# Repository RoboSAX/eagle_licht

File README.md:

# eagle_licht
Vereinfachte Platine für das Spielfeld des RoboSAX ab 2018

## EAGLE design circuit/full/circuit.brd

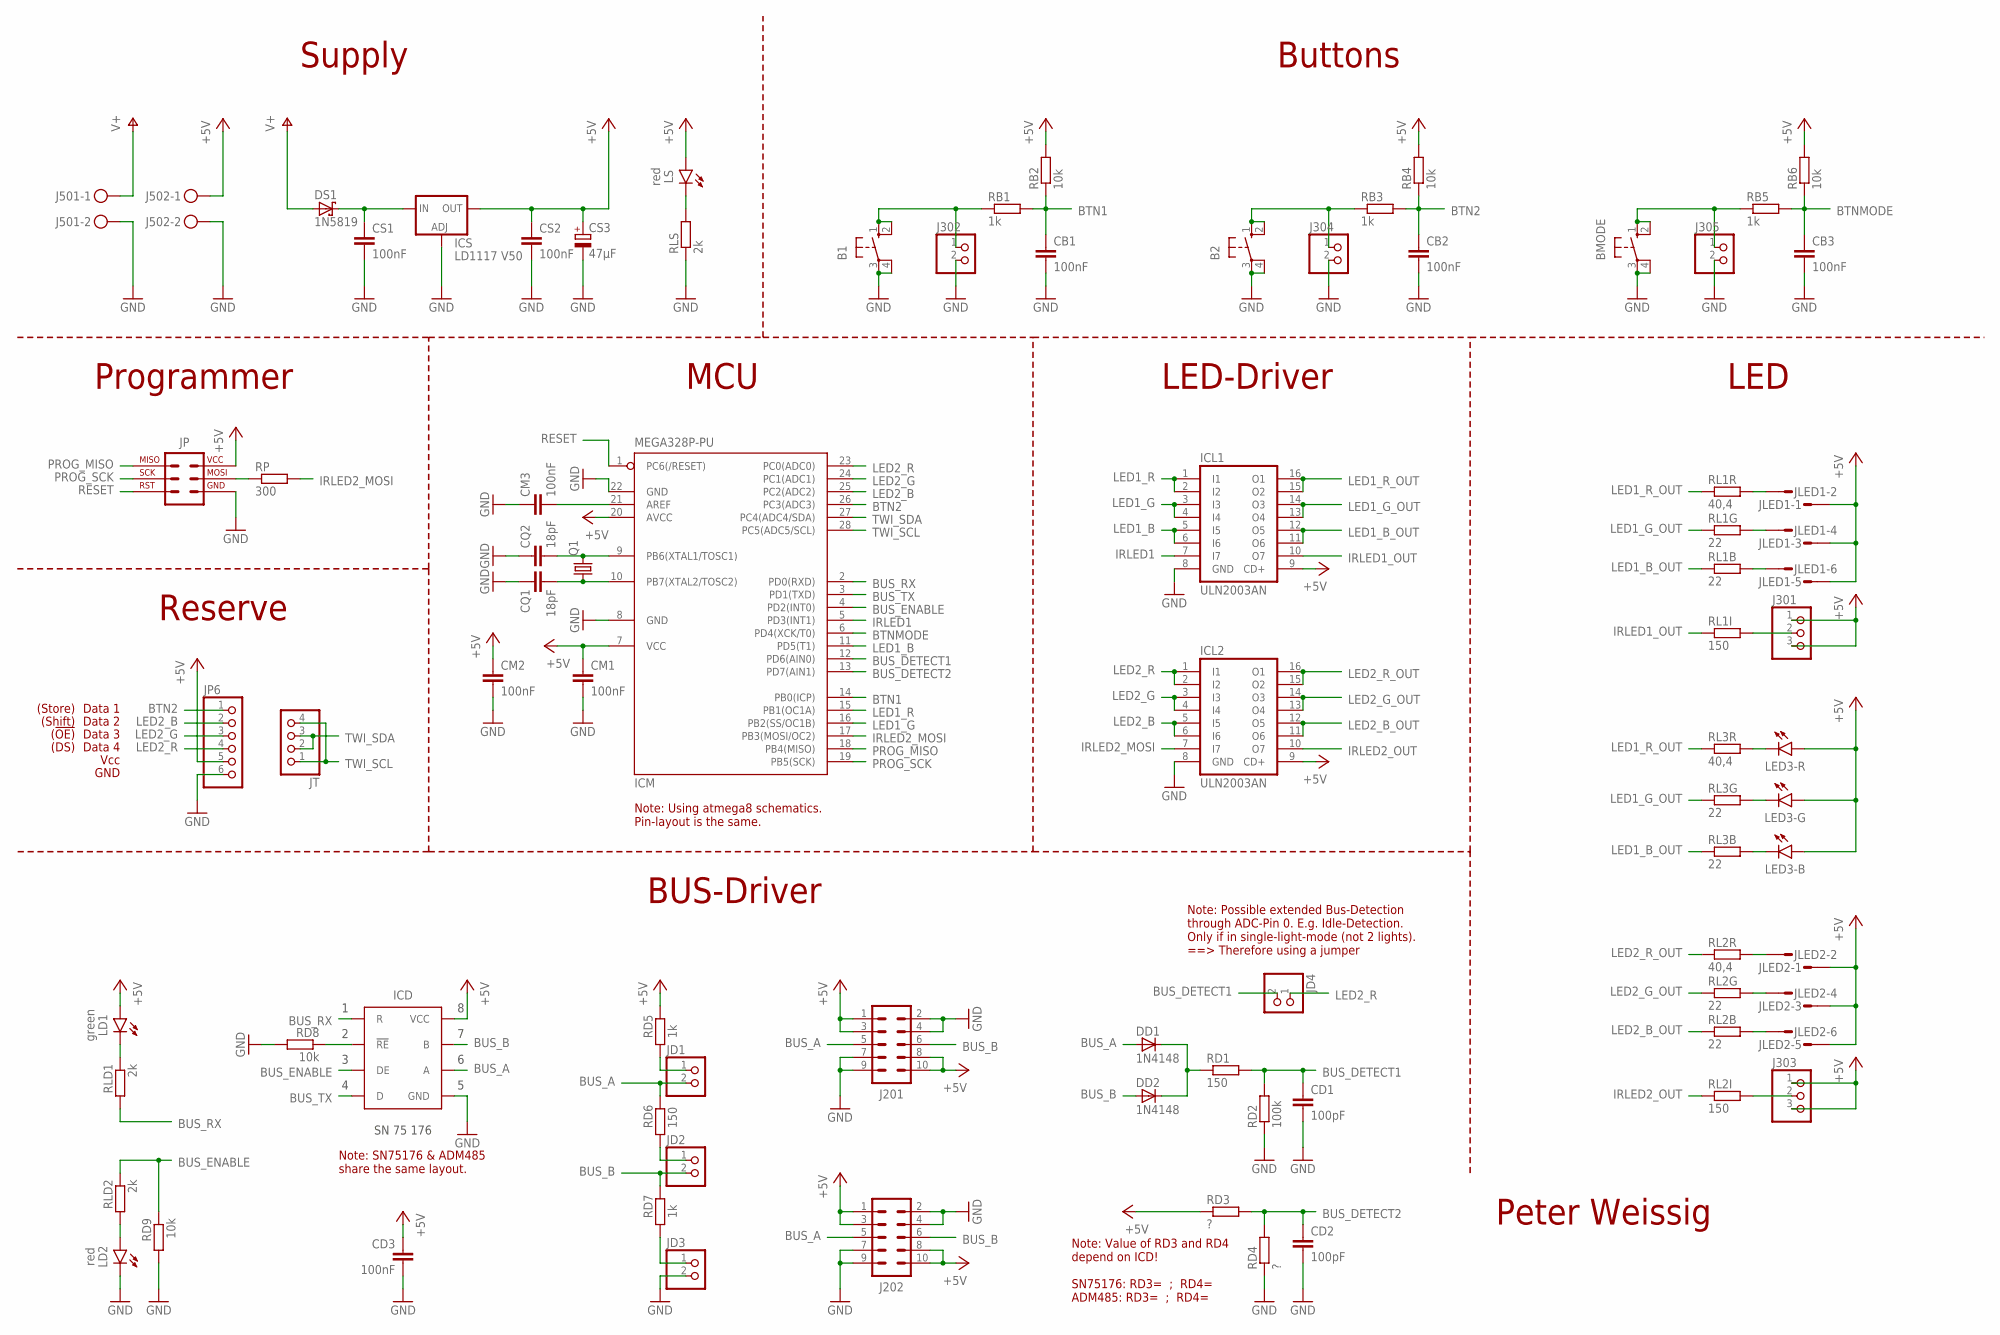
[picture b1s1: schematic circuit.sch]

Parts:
B1, B2: 10-XX; B3F-10XX
BMODE: 10-XX; B3F-10XX
CB1, CB2, CB3: 100nF; C025-025X050
CD1, CD2: 100pF; C025-025X050
CD3: 100nF; C025-025X050
CM1, CM2, CM3: 100nF; C025-025X050
CQ1, CQ2: 18pF; C025-025X050
CS1, CS2: 100nF; C025-025X050
CS3: 47µF; E2-5
DD1, DD2: 1N4148; DO35-7
DS1: 1N5819; DO41-7.6
ICD: DRIVER_RS485; IC_DIL08
ICL1, ICL2: ULN2003AN; DIL16
ICM: MEGA328P-PU; DIL28-3
ICS: LD1117 V50; TO220L1
J201, J202: STECKER_WANNE_10
J301, J303: PINHD-1X3; 1X03
J302, J304, J305: PINHD-1X2; 1X02
J501, J502: STECKER_SPG_2
JD1, JD2, JD3, JD4: PINHD-1X2; 1X02
JLED1, JLED2: MICROMATCH-6
JP: STECKER_ISP_6; STECKER_WANNE_6
JP6: PINHD-1X6/90; 1X06/90
JT: PINHD-1X4; 1X04
LD1: green; LED_3MM
LD2: red; LED_3MM
LED3: LED_3X; LED_TOP_PLCC6
LS: red; LED_3MM
Q1: CRYSTALHC49U70; HC49U70
RB1, RB3, RB5: 1k; 0207/10
RB2, RB4, RB6: 10k; 0207/10
RD1, RD6: 150; 0207/10
RD2: 100k; 0207/10
RD3, RD4: ?; 0207/10
RD5, RD7: 1k; 0207/10
RD8, RD9: 10k; 0207/10
RL1B, RL1G, RL2B, RL2G, RL3B, RL3G: 22; 0207/10
RL1I, RL2I: 150; 0207/10
RL1R, RL2R, RL3R: 40,4; 0207/10
RLD1, RLD2: 2k; 0207/10
RLS: 2k; 0207/10
RP: 300; 0207/10

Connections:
+5V: CD3.1, CM1.1, CM2.1, CS2.1, CS3.+, ICD.8 (VCC), ICL1.9 (CD+), ICL2.9 (CD+), ICM.7 (VCC), ICM.20 (AVCC), ICS.2 (OUT), J201.1, J201.3, J201.8, J201.10, J202.1, J202.3, J202.8, J202.10, J301.1, J301.3, J303.1, J303.3, J502.1, JLED1.1, JLED1.3, JLED1.5, JLED2.1, JLED2.3, JLED2.5, JP.2 (2_VCC), JP6.5, LD1.A, LED3.1 (A), LED3.3 (A), LED3.4 (A), LS.A, RB2.2, RB4.2, RB6.2, RD3.1, RD5.2
BTN1: CB1.1, ICM.14 (PB0(ICP)), RB1.2, RB2.1
BTN2: CB2.1, ICM.26 (PC3(ADC3)), JP6.1, RB3.2, RB4.1
BTNMODE: CB3.1, ICM.6 (PD4(XCK/T0)), RB5.2, RB6.1
BUS_A: DD1.A, ICD.6 (A), J201.5, J202.5, JD1.2, RD6.2
BUS_B: DD2.A, ICD.7 (B), J201.6, J202.6, JD2.2, RD7.2
BUS_DETECT1: CD1.1, ICM.12 (PD6(AIN0)), JD4.2, RD1.2, RD2.2
BUS_DETECT2: CD2.1, ICM.13 (PD7(AIN1)), RD3.2, RD4.2
BUS_ENABLE: ICD.3 (DE), ICM.4 (PD2(INT0)), RD9.1, RLD2.1
BUS_RX: ICD.1 (R), ICM.2 (PD0(RXD)), RLD1.2
BUS_TX: ICD.4 (D), ICM.3 (PD1(TXD))
GND: B1.3, B1.4 (P1), B2.3, B2.4 (P1), BMODE.3, BMODE.4 (P1), CB1.2, CB2.2, CB3.2, CD1.2, CD2.2, CD3.2, CM1.2, CM2.2, CM3.1, CQ1.1, CQ2.1, CS1.2, CS2.2, CS3.-, ICD.5 (GND), ICL1.8 (GND), ICL2.8 (GND), ICM.8 (GND), ICM.22 (GND), ICS.1 (ADJ), J201.2, J201.4, J201.7, J201.9, J202.2, J202.4, J202.7, J202.9, J302.2, J304.2, J305.2, J501.2, J502.2, JD3.2, JP.6 (6_GND), JP6.6, LD2.K (C), RD2.1, RD4.1, RD8.2, RD9.2, RLS.1
IRLED1: ICL1.7 (I7), ICM.5 (PD3(INT1))
IRLED1_OUT: ICL1.10 (O7), RL1I.1
IRLED2_MOSI: ICL2.7 (I7), ICM.17 (PB3(MOSI/OC2)), RP.2
IRLED2_OUT: ICL2.10 (O7), RL2I.1
LED1_B: ICL1.5 (I5), ICL1.6 (I6), ICM.11 (PD5(T1))
LED1_B_OUT: ICL1.11 (O6), ICL1.12 (O5), RL1B.1, RL3B.1
LED1_G: ICL1.3 (I3), ICL1.4 (I4), ICM.16 (PB2(SS/OC1B))
LED1_G_OUT: ICL1.13 (O4), ICL1.14 (O3), RL1G.1, RL3G.1
LED1_R: ICL1.1 (I1), ICL1.2 (I2), ICM.15 (PB1(OC1A))
LED1_R_OUT: ICL1.15 (O2), ICL1.16 (O1), RL1R.1, RL3R.1
LED2_B: ICL2.5 (I5), ICL2.6 (I6), ICM.25 (PC2(ADC2)), JP6.2
LED2_B_OUT: ICL2.11 (O6), ICL2.12 (O5), RL2B.1
LED2_G: ICL2.3 (I3), ICL2.4 (I4), ICM.24 (PC1(ADC1)), JP6.3
LED2_G_OUT: ICL2.13 (O4), ICL2.14 (O3), RL2G.1
LED2_R: ICL2.1 (I1), ICL2.2 (I2), ICM.23 (PC0(ADC0)), JD4.1, JP6.4
LED2_R_OUT: ICL2.15 (O2), ICL2.16 (O1), RL2R.1
unnamed: B1.1 (S), B1.2 (S1), J302.1, RB1.1
unnamed: CS1.1, DS1.C, ICS.3 (IN)
unnamed: B2.1 (S), B2.2 (S1), J304.1, RB3.1
unnamed: BMODE.1 (S), BMODE.2 (S1), J305.1, RB5.1
unnamed: CQ1.2, ICM.10 (PB7(XTAL2/TOSC2)), Q1.1
unnamed: CQ2.2, ICM.9 (PB6(XTAL1/TOSC1)), Q1.2
unnamed: LS.K (C), RLS.2
unnamed: CM3.2, ICM.21 (AREF)
unnamed: JLED1.2, RL1R.2
unnamed: JLED1.4, RL1G.2
unnamed: JLED1.6, RL1B.2
unnamed: JLED2.2, RL2R.2
unnamed: JLED2.4, RL2G.2
unnamed: JLED2.6, RL2B.2
unnamed: J303.2, RL2I.2
unnamed: J301.2, RL1I.2
unnamed: LED3.6 (C), RL3R.2
unnamed: LED3.2 (C), RL3G.2
unnamed: LED3.5 (C), RL3B.2
unnamed: JD1.1, RD5.1
unnamed: ICD.2 (!RE), RD8.1
unnamed: JD2.1, RD6.1
unnamed: LD1.K (C), RLD1.1
unnamed: JD3.1, RD7.1
unnamed: DD1.C, DD2.C, RD1.1
unnamed: LD2.A, RLD2.2
PROG_MISO: ICM.18 (PB4(MISO)), JP.1 (1_MISO)
PROG_MOSI_1: JP.4 (4_MOSI), RP.1
PROG_SCK: ICM.19 (PB5(SCK)), JP.3 (3_SCK)
RESET: ICM.1 (PC6(/RESET)), JP.5 (5_RST)
TWI_SCL: ICM.28 (PC5(ADC5/SCL)), JT.1, JT.4
TWI_SDA: ICM.27 (PC4(ADC4/SDA)), JT.2, JT.3
V+: DS1.A, J501.1

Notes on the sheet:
Peter Weissig
Supply
Buttons
MCU
Note: Using atmega8 schematics. Pin-layout is the same.
LED-Driver
LED
Reserve
GND
Vcc
(Store)
Data 1
Data 2
Data 3
Data 4
(Shift)
(!OE)
(DS)
Programmer
BUS-Driver
Note: SN75176 & ADM485 share the same layout.
Note: Value of RD3 and RD4 depend on ICD! SN75176: RD3= ; RD4= ADM485: RD3= ; RD4=
Note: Possible extended Bus-Detection through ADC-Pin 0. E.g. Idle-Detection. Only if in single-light-mode (not 2 lights). ==> Therefore using a jumper

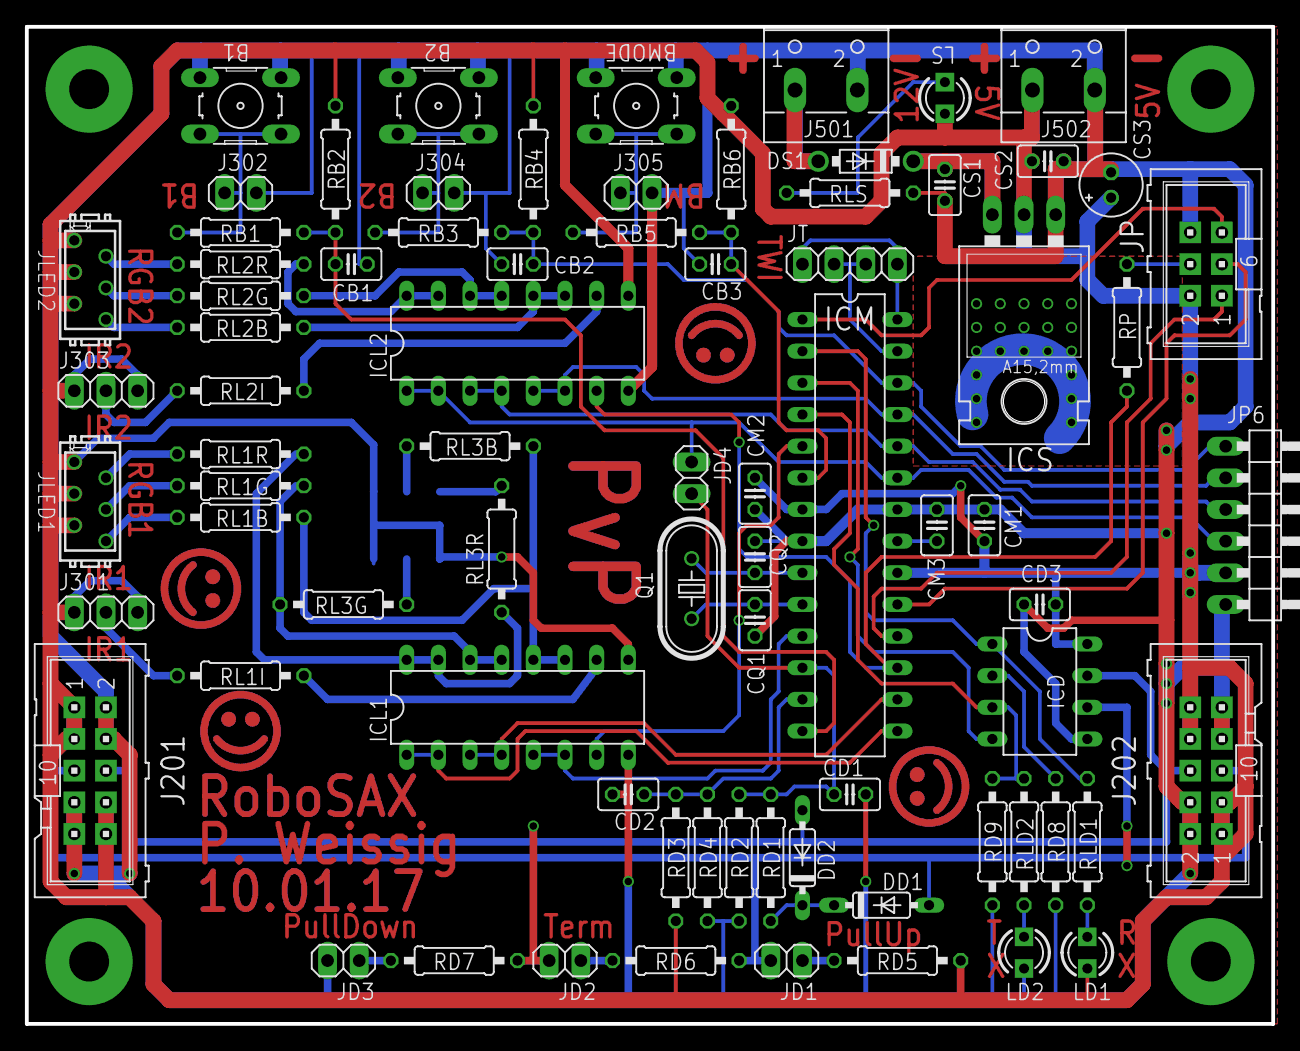
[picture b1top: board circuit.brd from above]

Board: 2 copper layers, 100.0 x 80.0 mm, 78 parts (1 on the bottom side), 61 nets.

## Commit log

2018-01-08 initial commit + added simple circuit (no layout yet)
2018-01-08 updated circuit + added layout (not done yet)
2018-01-10 updated circuit + layout is done + updated export files
2018-01-10 finished layout and exported data
2018-01-11 added part-list and approximate pricing
2018-01-13 bugfixed partlist (changed some numbers; added 300R)
2018-01-22 monir bugfixes + ULN2003 has socket of 2x8 not 2x7 (updated part-list) + switched label of resistors (RD8 and RLD1) + updated LED3 (removed solder resist) + moved 2 labels, so that they will be visib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
2018-01-29 updated circuit (added simplified version & minor bugfixes)
2018-02-11 switched color of LD1 and LD2 in full version
2018-02-25 moved & copied .gitignore file
